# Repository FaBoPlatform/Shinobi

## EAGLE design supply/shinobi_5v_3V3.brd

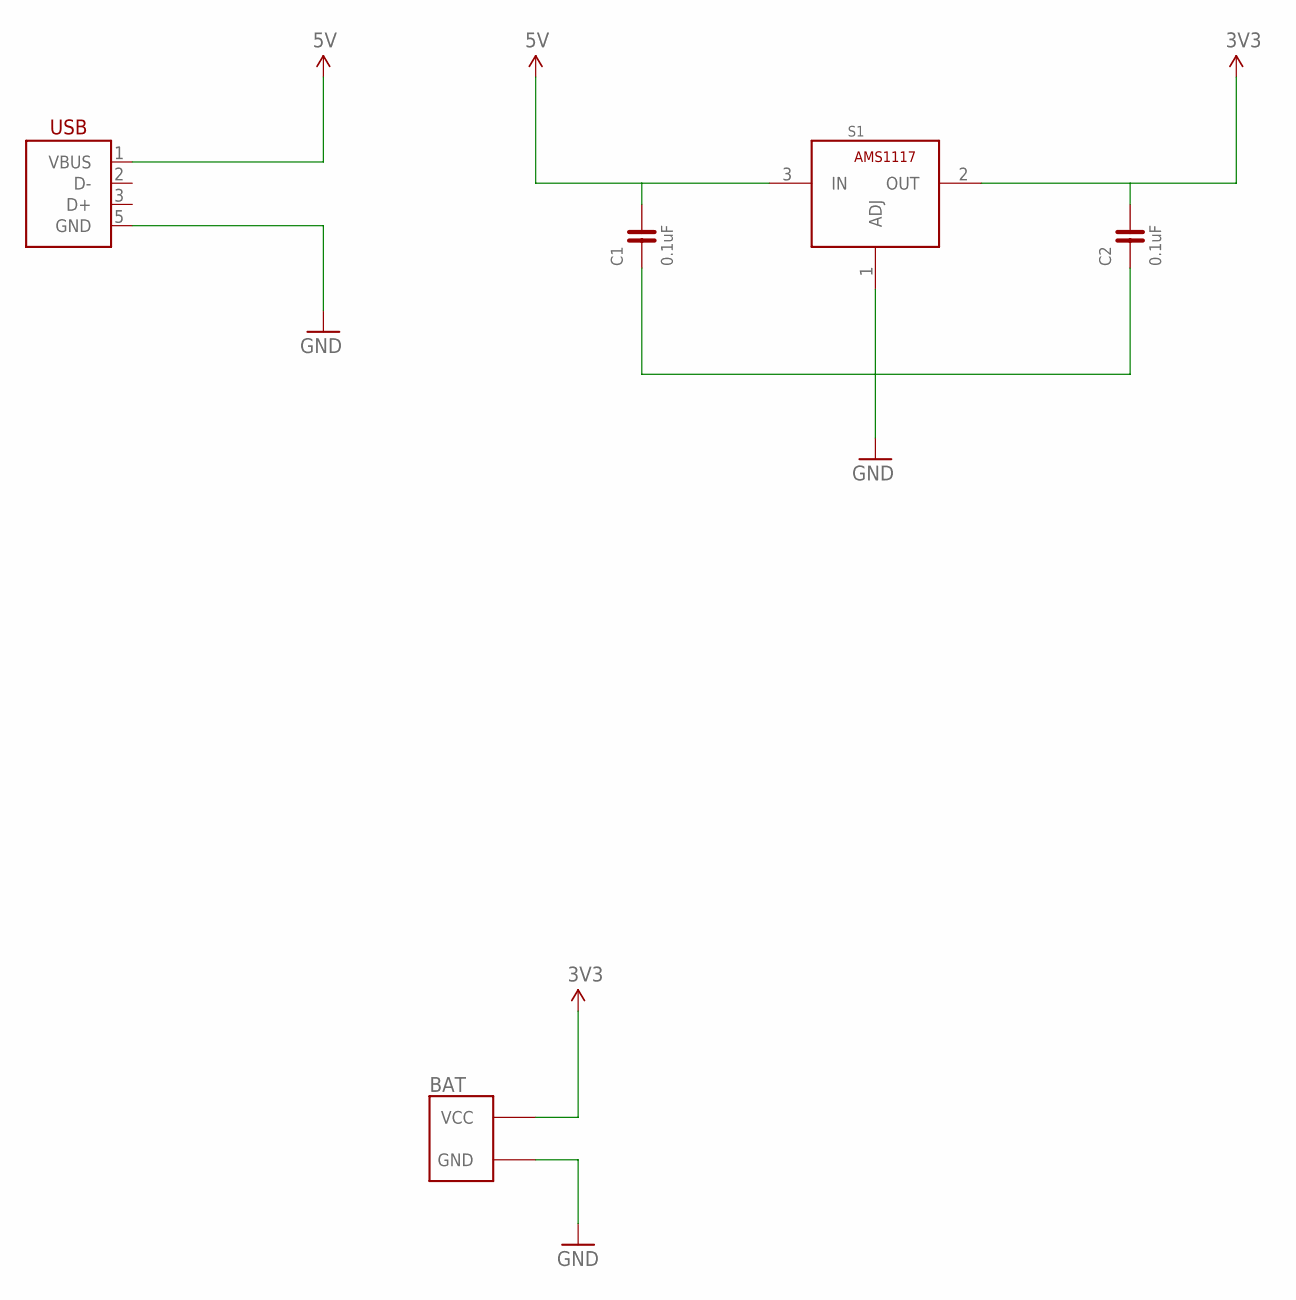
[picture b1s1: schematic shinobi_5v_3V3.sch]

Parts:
BAT: FABO_BRICK_2PIN_SIDE; FABO_BRICK_2PIN_S02B−PASK-2_SILK
C1, C2: 0.1uF; 0603
S1: AMS1117; SOT-223-3
USB1: USB-MICRO_B_SMT_HIROSE; ZX62R-B-5P

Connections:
3V3: BAT.VCC, C2.2, S1.2 (OUT)
5V: C1.2, S1.3 (IN), USB1.1 (VBUS)
GND: BAT.GND, C1.1, C2.1, S1.1 (ADJ), USB1.5 (GND)

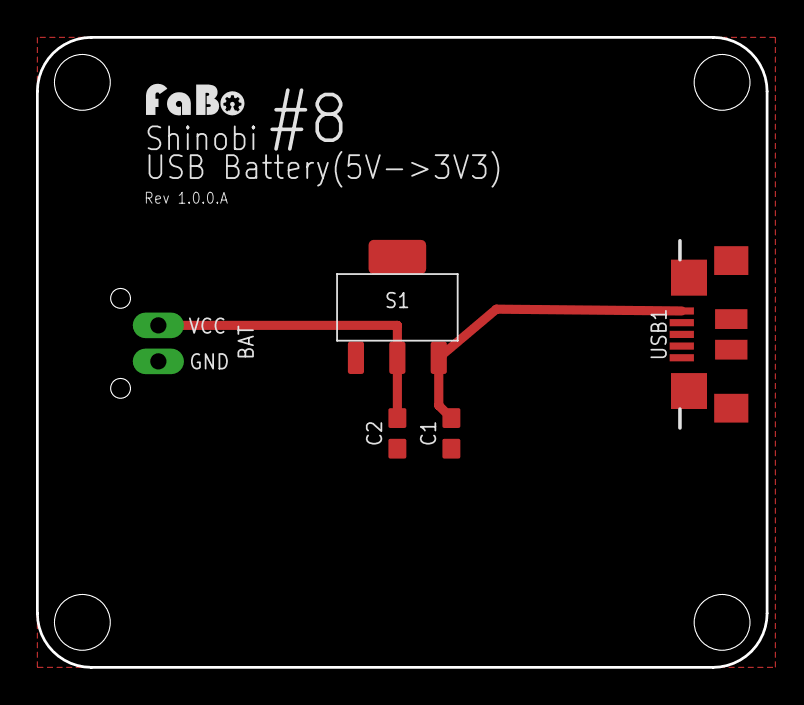
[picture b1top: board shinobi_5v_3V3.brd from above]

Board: 2 copper layers, 40.5 x 35.0 mm, 7 parts (0 on the bottom side), 3 nets.

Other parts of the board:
U$2: LOGO_FABO_S
U$3: FABO-SHINOBI

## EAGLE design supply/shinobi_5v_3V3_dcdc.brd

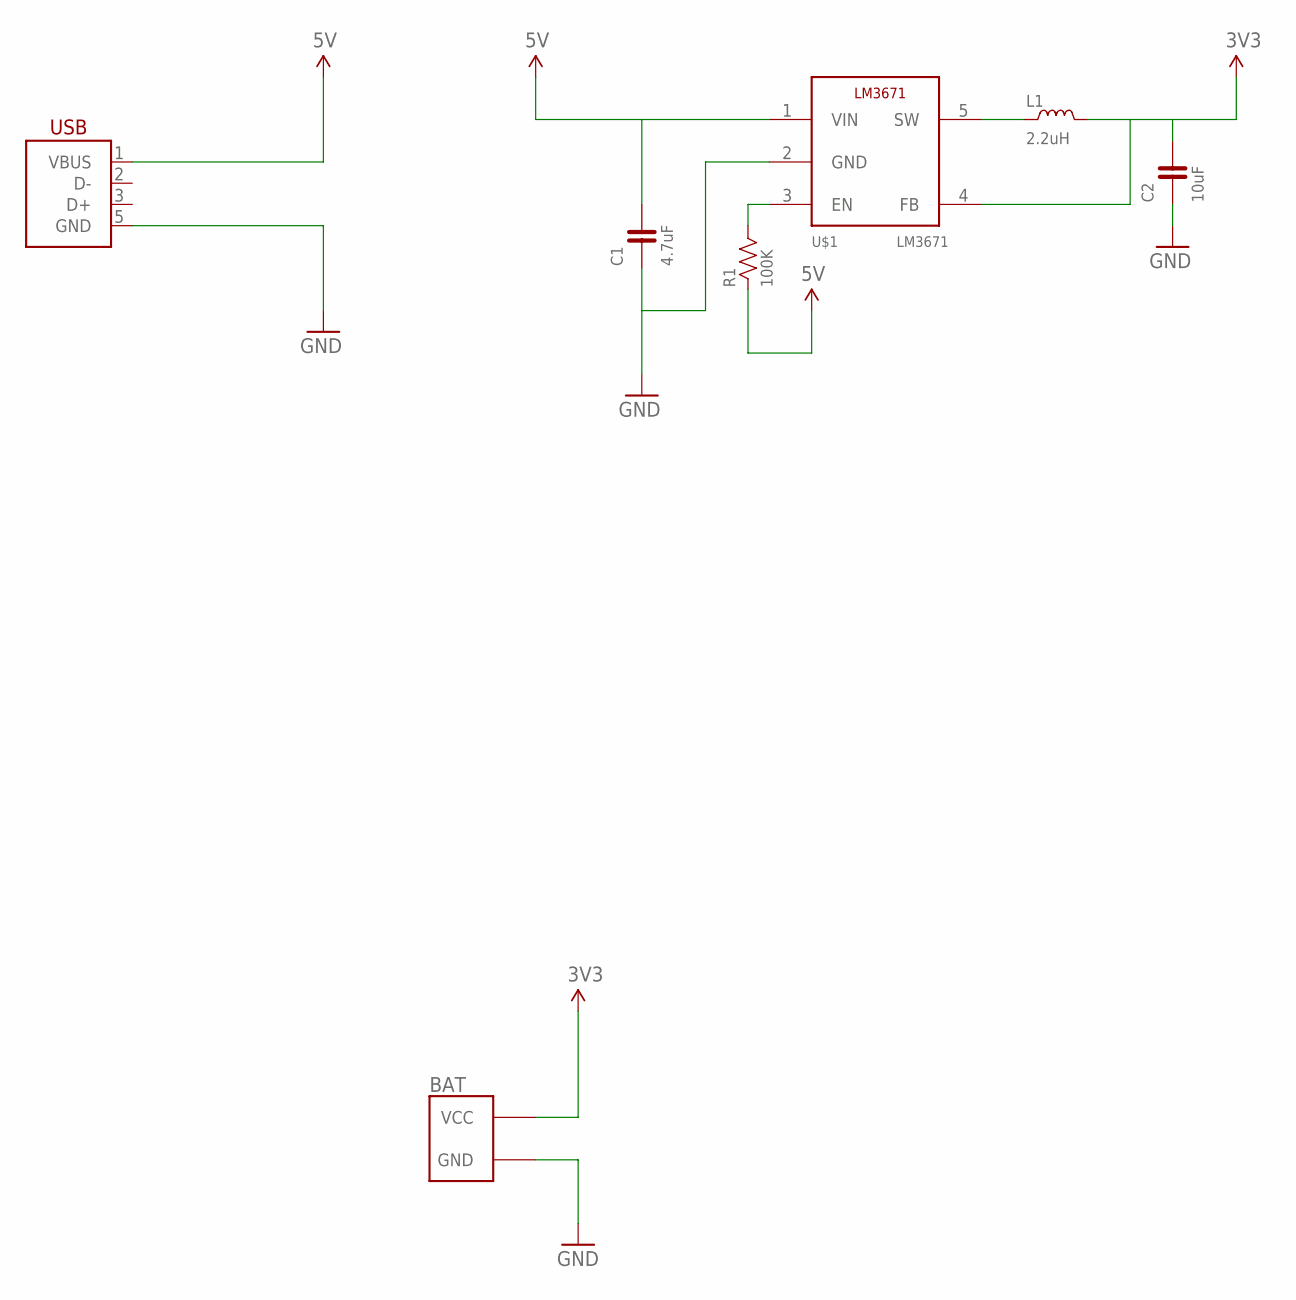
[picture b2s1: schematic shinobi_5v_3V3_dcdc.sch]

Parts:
BAT: FABO_BRICK_2PIN_SIDE; FABO_BRICK_2PIN_S02B−PASK-2_SILK
C1: 4.7uF; 0603
C2: 10uF; 0603
L1: 2.2uH; 2.4X2.4
R1: 100K; 0603
U$1: LM3671
USB1: USB-MICRO_B_SMT_HIROSE; ZX62R-B-5P

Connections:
3V3: BAT.VCC, C2.2, L1.P$2 (2), U$1.4 (FB)
5V: C1.2, R1.1, U$1.1 (VIN), USB1.1 (VBUS)
GND: BAT.GND, C1.1, C2.1, U$1.2 (GND), USB1.5 (GND)
unnamed: R1.2, U$1.3 (EN)
unnamed: L1.P$1 (1), U$1.5 (SW)

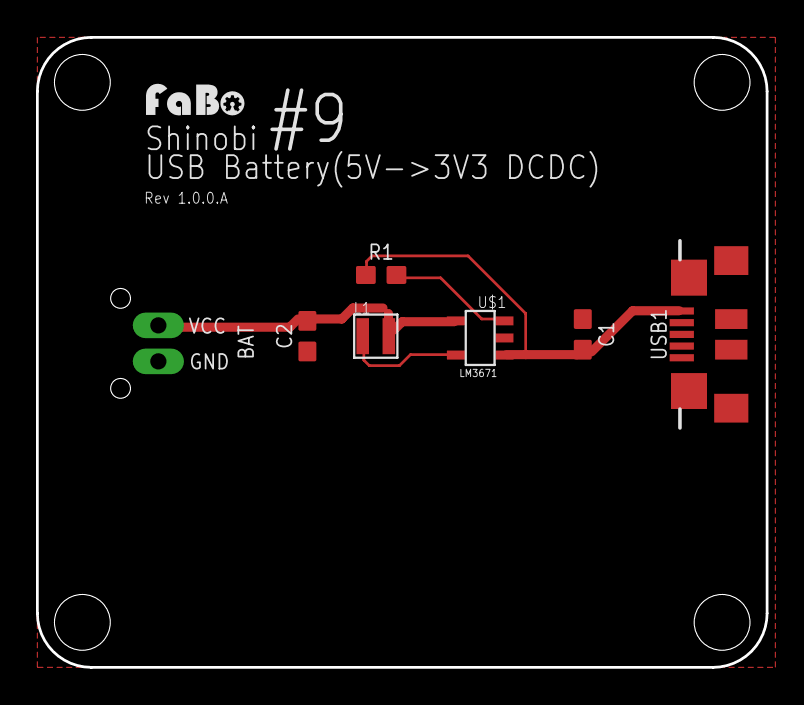
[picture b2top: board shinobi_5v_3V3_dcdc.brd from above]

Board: 2 copper layers, 40.5 x 35.0 mm, 9 parts (0 on the bottom side), 5 nets.

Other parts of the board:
U$2: LOGO_FABO_S
U$3: FABO-SHINOBI

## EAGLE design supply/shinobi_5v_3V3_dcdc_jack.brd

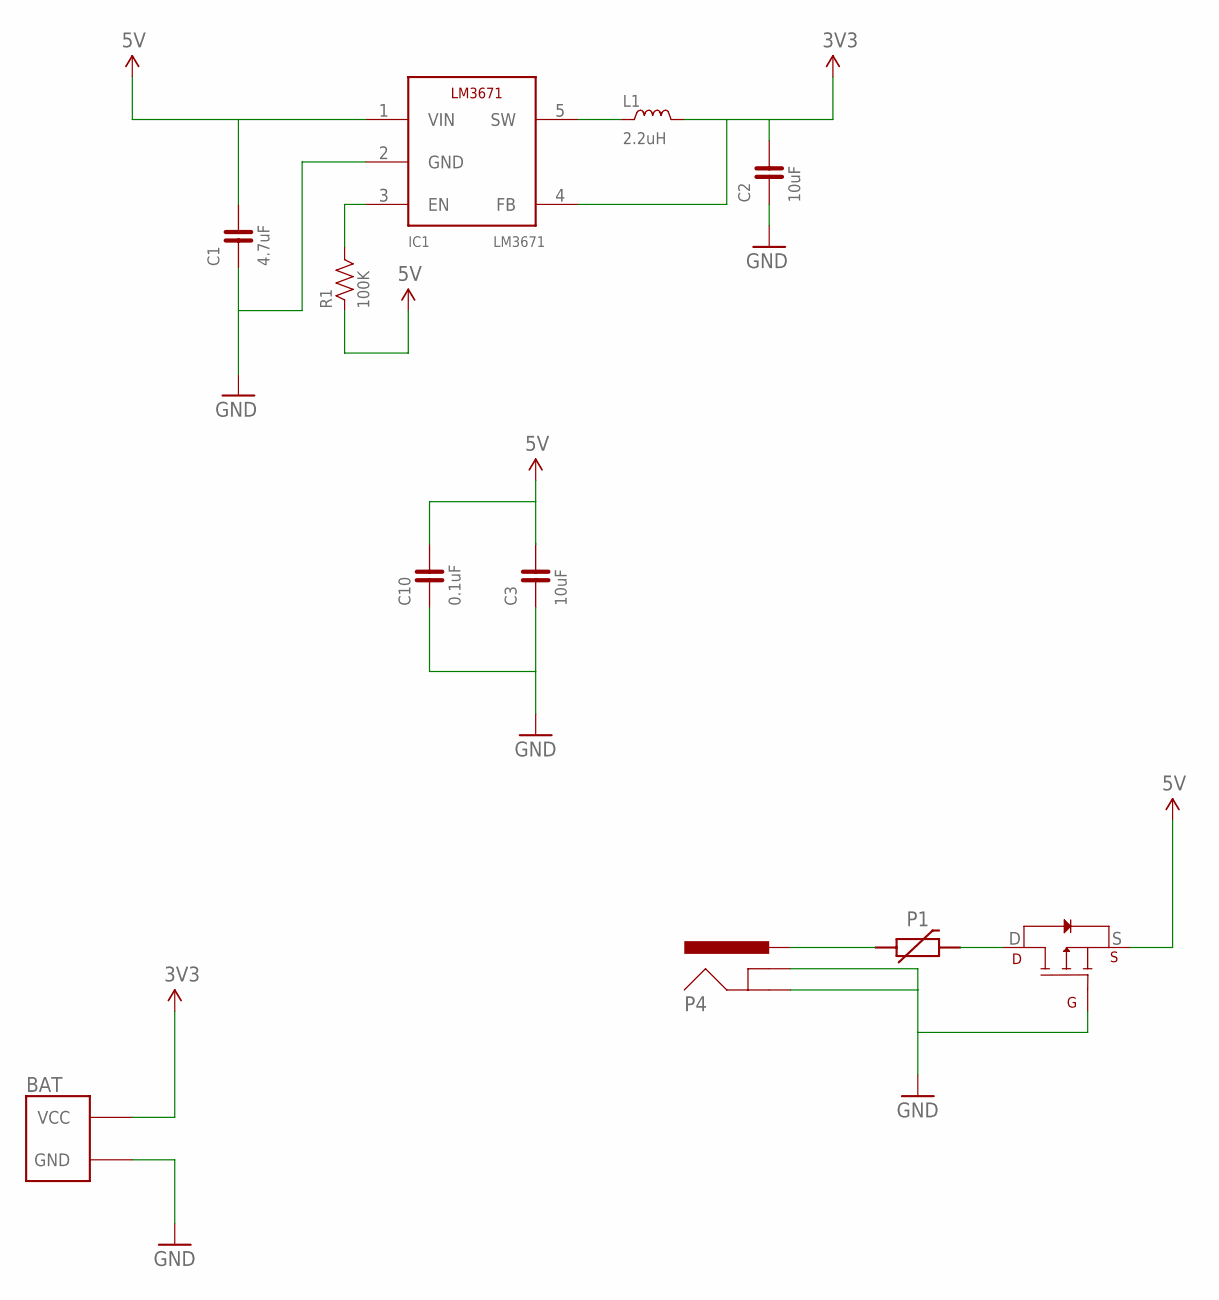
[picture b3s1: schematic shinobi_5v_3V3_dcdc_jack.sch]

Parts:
BAT: FABO_BRICK_2PIN_SIDE; FABO_BRICK_2PIN_S02B−PASK-2_SILK
C1: 4.7uF; 0603
C2, C3: 10uF; 0603
C10: 0.1uF; 0603
IC1: LM3671
L1: 2.2uH; 2.4X2.4
M1: AOD417
P1: POLYSWITCH1210; 1210
P4: DC-JACK2DC-G232-B66; 2DC-G213-B66
R1: 100K; 0603

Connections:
3V3: BAT.VCC, C2.2, IC1.4 (FB), L1.P$2 (2)
5V: C1.2, C3.2, C10.2, IC1.1 (VIN), M1.S, R1.1
GND: BAT.GND, C1.1, C2.1, C3.1, C10.1, IC1.2 (GND), M1.G, P4.GND, P4.GND-BREAKE@2 (GNDBREAK), P4.GND-BREAKER@1 (GNDBREAK), P4.GND-BREAKER@3 (GNDBREAK), P4.GND-BREAKER@4 (GNDBREAK)
unnamed: IC1.3 (EN), R1.2
unnamed: IC1.5 (SW), L1.P$1 (1)
unnamed: P1.P$1 (1), P4.VCC (PWR)
unnamed: M1.D, P1.P$2 (2)

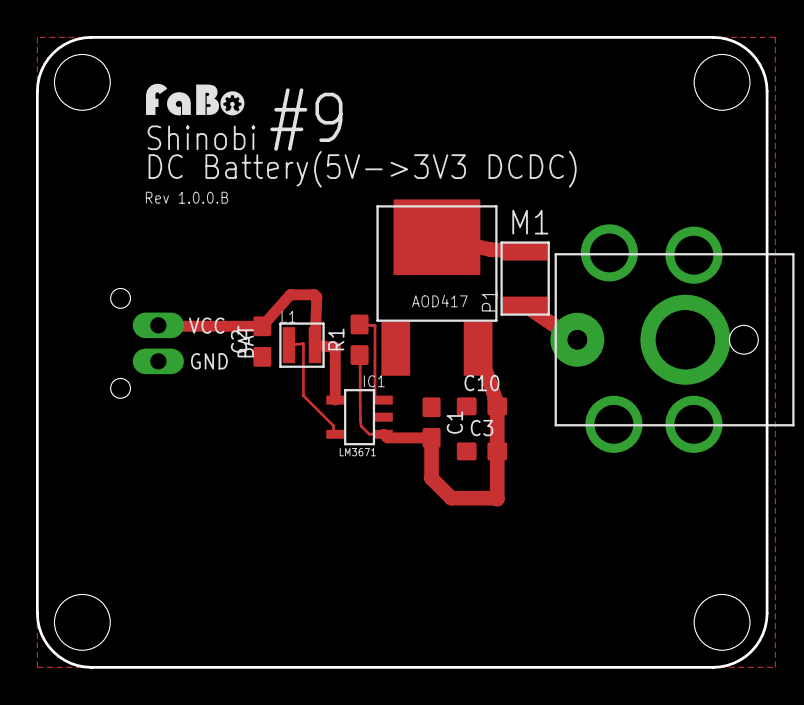
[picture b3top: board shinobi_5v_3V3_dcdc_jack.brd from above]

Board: 2 copper layers, 40.5 x 35.0 mm, 13 parts (0 on the bottom side), 7 nets.

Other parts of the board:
U$2: LOGO_FABO_S
U$3: FABO-SHINOBI

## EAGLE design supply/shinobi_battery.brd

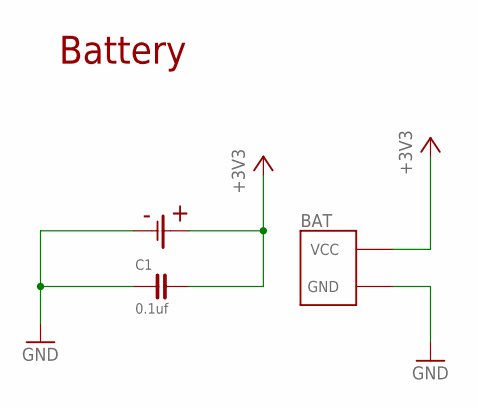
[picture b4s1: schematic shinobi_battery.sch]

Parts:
BAT: FABO_BRICK_2PIN_SIDE; FABO_BRICK_2PIN_S02B−PASK-2_SILK
C1: 0.1uf; 0603
U$1: CH031-2477FL

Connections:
+3V3: BAT.VCC, C1.2, U$1.+
GND: BAT.GND, C1.1, U$1.-

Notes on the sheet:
Battery

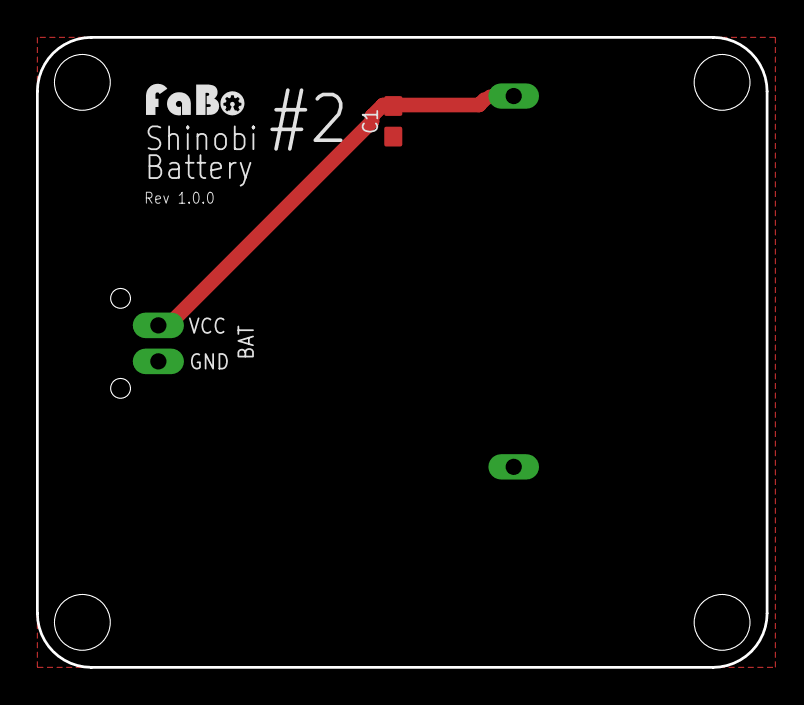
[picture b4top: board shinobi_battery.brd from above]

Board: 2 copper layers, 40.5 x 35.0 mm, 5 parts (0 on the bottom side), 2 nets.

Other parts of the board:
U$2: LOGO_FABO_S
U$3: FABO-SHINOBI

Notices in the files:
parts and their libraries:
FaBo-Logo: Released under the Creative Commons Attribution-ShareAlike 4.0 License
https://creativecommons.org/licenses/by-sa/4.0
FaBo-etc: Released under the Creative Commons
